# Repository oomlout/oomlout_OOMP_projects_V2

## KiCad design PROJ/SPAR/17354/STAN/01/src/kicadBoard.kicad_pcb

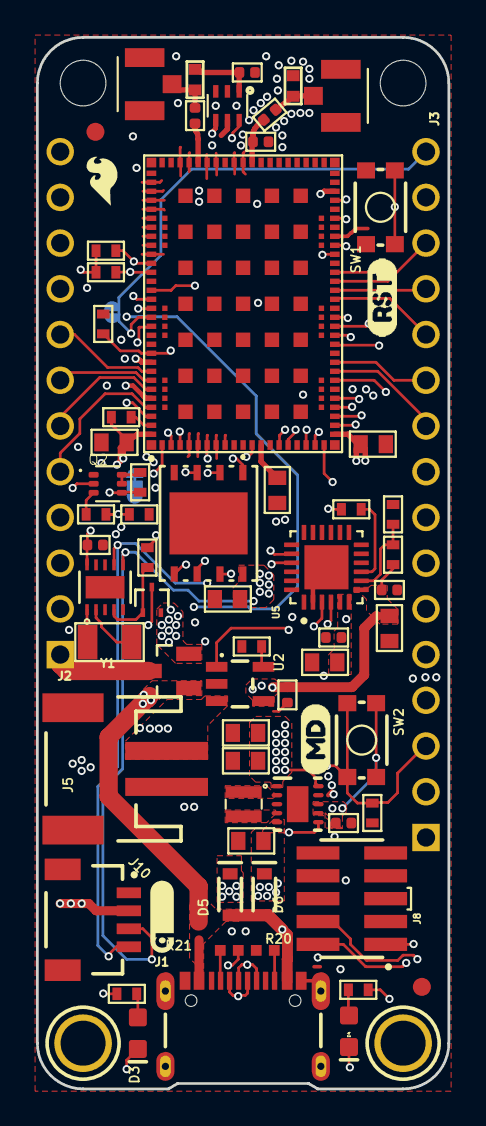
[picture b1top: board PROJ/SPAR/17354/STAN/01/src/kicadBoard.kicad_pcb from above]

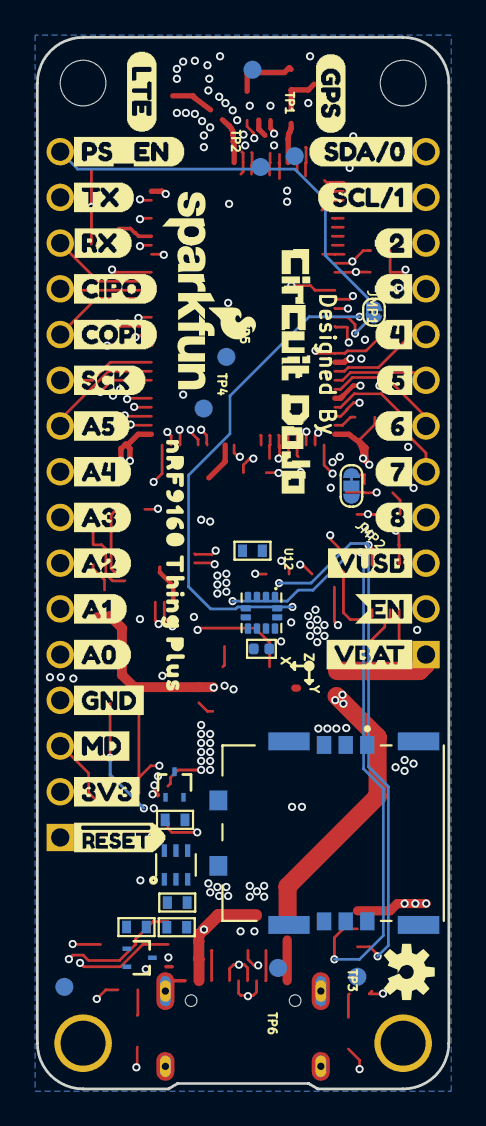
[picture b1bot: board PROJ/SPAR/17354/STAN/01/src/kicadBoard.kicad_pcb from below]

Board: 4 copper layers, 22.9 x 58.4 mm, 130 parts (55 on the bottom side), 79 nets.

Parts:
@HOLE0, @HOLE1: (no value)
C1, C2: 15p; CAPC1005X55N
C3, C8, C9, C10, C13, C15: 4.7u; C0603
C4, C5, C7: 10u; C0603
C6, C14, C16, C17, C20: 0.1u; CAPC1005X55N
C11: 1u; CAPC1005X55N
C12, C19: 56p; CAPC1005X55N
D3: BLUE; LED-0603
D4: Yellow; LED-0603
D5, D6: 1A/23V/620mV; SOD-323
J1: USB Female C; USB-C-16P_4LAYER-PADS
J2: CON-HEADER-1X12-MALE-PIN
J3: CON-HEADER-1X16-MALE-PIN
J4, J7: CON-1909763-1; TE_1909763-1
J5: JST-2-SMD
J6: CON-SIM-104224-0820; MOLEX_104224-0820
J8: CON-FTSH-105-XX-X-DV; SAMTEC_FTSH-105-XX-X-DV
J10: QWIIC_RIGHT_ANGLE; JST04_1MM_RA
JMP1: JUMPER-NC; JUMPER-ROUND-NC
JMP2: JUMPER-3/1; JUMPER-ROUND-3-NO-R
L1: 39n; IND0402_22N_TAI
L2: 1.5u; IND-2P0X2P0X1P2
L4: 68n; IND0402_22N_TAI
LOGO5: OSHW-LOGOS; OSHW-LOGO-S
PCB1: PCB-NRF91-FEATHER; PLACEHOLDER
Q1: MOSFET-P-SC89; DIO_RB558WMF-L
Q2: MOSFET-DUAL-COMP-SOT563; SOT50P160X60-6N
Q3: MOSFET-P-20V-4.7A-SOT23; SOT23
Q4, Q5: MOSFET-N-SC89; DIO_RB558WMF-L
R1, R3, R5, R6, R7, R8, R10, R13, R23: 100k; R0402-M
R2, R9, R19: 1M; R0402-M
R4: 1k; R0402-M
R11, R14: 330; R0402-M
R12: 2k; R0402-M
R15: 22k; R0402-M
R16: 33k; R0402-M
R17, R18: 10k; R0402-M
R20, R21: 5.1k; 0402-TIGHT
SW1, SW2: TACTILE_SWITCH_SMD_4.6X2.8MM
TP1, TP2, TP3, TP4, TP5, TP6: TP-1SIDE-1P0; TP-1P0
U1: MOD-NRF9160-SICA-R; NORDIC_NRF9160-SICA-R
U2: MCP73831; SOT23-5
U3: IC-TPS63031DSKR; DSK0010A
U4: POWER-SWITCH-MIC94092YC6; SOT363
U5: IC-CP2102N-A02-GQFN24R; QFN50P400X400X80-25N
U6: FLASH-WSON; WIN_ZP-8-L
U8: IC-PCF85063ATL/1; DFN10_2P7X2P7-L
U9: IC-BAV70S; SOT363
U12: IC-LIS2DH12TR; PQFN50P200X200100-12N
U$1: SFE_LOGO_NAME_FLAME_.1
U$2: LOGO-CIRCUITDOJO
U$3, U$4, U$24, U$35: FIDUCIAL-1MM
U$5: A3L-LOC
U$6: QWIIC_4MM
U$7: RST0
U$8: PS_EN0
U$9, U$14: MD0
U$10: 20
U$11: 30
U$12: SCL#11
U$13: SDA#00
U$15: SFE_LOGO_FLAME_.1
U$16: TX0
U$17: RX0
U$18: SCK0
U$19: CIPO0
U$20: COPI0
U$21: GPS0
U$22: LTE0
U$23: NRF9160_THING_PLUS0
U$31, U$32: MOUNTING-HOLE-2.5MM-PLATED
U$69: GND12
U$71: 3V314
U$72: #RESET15
U$73: VUSB25
U$74: EN26
U$75: VBAT27
U$83: A56
U$84: A47
U$85: A38
U$86: A29
U$87: A110
U$88: A011
U$89: 412
U$90: 513
U$91: 614
U$92: 715
U$93: 816
Y1: XTAL-ABS07AIG-32.768KHZ-7-T; XTAL320X150X90

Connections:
+3V3: C3.1, C4.1, C5.1, C8.1, C10.1, C20.1, J3.2, J8.1, J10.2, R9.2, R11.2, R14.2, R17.2, R18.2, R23.2, U1.12, U1.22, U1.102, U3.1, U3.10, U4.4, U6.8, U12.9, U12.10
ANT: C1.2, C2.1, U1.61
ANT_FILT: C1.1, J4.1, L1.2
CHRG: D4.C, U2.1
COEX0/LNA_EN: R1.2, U1.93, U4.6
CP212_VBUS: R15.1, R16.2, U5.8
CP2102N-VDD: C15.1, C16.1, R4.2, U5.5, U5.6
CP2102N-~RST: R4.1, U5.9
DIFF_N: J1.A7, J1.B7, U5.4
DIFF_P: J1.A6, J1.B6, U5.3
FLASH_CS: U1.4, U6.1
FLASH_HOLD: U1.18, U6.7
FLASH_SCK: U1.19, U6.6
FLASH_SI: U1.16, U6.5
FLASH_SO: U1.86, U6.2
FLASH_WP: U1.15, U6.3
GND: C2.2, C3.2, C4.2, C5.2, C6.2, C7.2, C8.2, C9.2, C10.2, C11.2, C13.2, C14.2, C15.2, C16.2, C17.2, C19.2, C20.2, J1.GND, J1.GND2, J1.SHLD1, J1.SHLD2, J1.SHLD3, J1.SHLD4, J3.4, J4.2, J4.3, J5.1, J6.G1, J6.G2, J6.G3, J6.G4, J6.S4, J7.2, J7.3, J8.3, J8.5, J8.9, J10.1, L1.1, Q2.1, Q4.2, Q5.2, R1.1, R2.1, R7.1, R8.1, R12.1, R13.1, R16.1, R19.1, R20.1, R21.1, SW1.3, SW1.4, U1.1, U1.5, U1.6, U1.7, U1.8, U1.9, U1.11, U1.14, U1.17, U1.21, U1.27, U1.31, U1.36, U1.41, U1.44, U1.47, U1.50, U1.52, U1.56, U1.60, U1.62, U1.63, U1.65, U1.66, U1.68, U1.69, U1.72, U1.74, U1.75, U1.76, U1.77, U1.78, U1.79, U1.80, U1.81, U1.82, U1.85, U1.90, U1.94, U1.98, U1.103_1, U1.103_2, U1.103_3, U1.103_4, U1.103_5, U1.103_6, U1.103_7, U1.103_8, U1.103_9, U1.103_10, U1.103_11, U1.103_12, U1.103_13, U1.103_14, U1.103_15, U1.103_16, U1.103_17, U1.103_18, U1.103_19, U1.103_20, U1.103_21, U1.103_22, U1.103_23, U1.103_24, U1.103_25, U1.103_26, U1.103_27, U1.103_28, U1.103_29, U1.103_30, U1.103_31, U1.103_32, U1.103_33, U1.103_34, U1.103_35, U2.2, U3.3, U3.9, U3.11, U4.2, U4.5, U5.2, U5.25, U6.4, U8.3, U8.5, U8.11, U12.3, U12.5, U12.6, U12.7, U12.8
GPS: C12.1, U1.67
GPS_ANT: C12.2, J7.1, L4.2
LNA_SW_OUT: C19.1, L4.1, U4.1
MODE/WAKE: J3.3, Q4.1, R13.2, SW2.3, SW2.4, U9.4
unnamed: L2.P$1, U3.4
unnamed: L2.P$2, U3.2
unnamed: J1.A5, R21.2
unnamed: R9.1, U1.101
unnamed: C9.1, U1.13
unnamed: Q2.3, R3.2
unnamed: Q2.5, Q2.6, R10.1
unnamed: D3.A, R11.1
unnamed: J1.B5, R20.2
unnamed: U8.1, Y1.2
unnamed: R23.1, U12.2
unnamed: JMP1.P$1, U12.12
unnamed: D4.A, R14.1
unnamed: U8.2, Y1.1
NRF_PS_EN_JMP: JMP2.P$2, U9.1
P0.00/D4: J2.8, U1.95
P0.01/D5: J2.7, U1.96
P0.02/D6: J2.6, U1.97
P0.03/D7: D3.C, J2.5, U1.99
P0.04/D8: J2.4, U1.100
P0.05/USB_UART_RX: U1.2, U5.21
P0.06/USB_UART_TX: U1.3, U5.20
P0.12/MD: Q4.3, U1.20
P0.13/A0: J3.5, U1.23
P0.14/A1: J3.6, U1.24
P0.15/A2: J3.7, U1.25
P0.16/A3: J3.8, U1.26
P0.17/A4: J3.9, U1.28
P0.18/A5: J3.10, U1.29
P0.19/SCK: J3.11, U1.30
P0.20/VBAT_MEAS: R3.1, R8.2, U1.35
P0.21/COPI: J3.12, U1.37
P0.22/CIPO: J3.13, U1.38
P0.23/RX: J3.14, U1.39
P0.24/TX: J3.15, U1.40
P0.25/VBAT_MEAS_EN: Q2.2, U1.42
P0.26/SDA: J2.12, J10.3, R17.1, U1.83, U8.6, U12.4
P0.27/SCL: J2.11, J10.4, R18.1, U1.84, U8.7, U12.1
P0.29/D2: J2.10, JMP1.P$2, U1.87
P0.30/D3: J2.9, U1.88
P0.31/NRF_PS_EN: J3.16, JMP2.P$3, U1.89
PROG: R12.2, U2.5
PS_EN: Q5.3, R5.1, U3.6
PS_EN_CC: R2.2, R5.2, U9.3, U9.6
RTC_INT: Q1.1, R6.1, U8.4
RTC_PS_EN: Q1.3, U9.5
SIM_CLK: J6.S3, TP3.TP, U1.46
SIM_IO: J6.S6, TP6.TP, U1.48
SIM_RST: J6.S2, TP4.TP, U1.43
SIM_VCC: J6.S1, TP5.TP, U1.49
SWCLK: J8.4, TP2.TP, U1.33
SWDIO: J8.2, TP1.TP, U1.34
VBAT: J2.1, J5.2, Q2.4, Q3.3, R10.2, U2.3
VBUS: C11.1, C13.1, C14.1, D5.A, D6.A, J1.VBUS1, J1.VBUS2, Q3.1, R7.2, R15.2, U2.4, U5.7, U9.2
VCC_5V0: D5.C, J2.3
VSYS: C6.1, C7.1, C17.1, D6.C, JMP2.P$1, Q1.2, Q3.2, R6.2, SW2.1, SW2.2, U3.5, U3.7, U3.8, U8.10
~EN: J2.2, Q5.1, R19.2
~RESET: J3.1, SW1.1, SW1.2, U1.32

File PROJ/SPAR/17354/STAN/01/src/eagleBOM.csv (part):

"Part";"Value";"Device";"Package";"Description";"ALIAS";"AVAILABILITY";"CURRENT";"DESC";"DESCRIPTION";"DIGIKEYPN";"MF";"MPN";"PACKAGE";"POWER";"PRICE";"PROD_ID";"PURCHASE-URL";"SF_ID";"TEMPHIGH";"TEMPLOW";"TOLERANCE";"VALUE";"VOLTHIGH";"VOLTLOW";
"C1";"15p";"CAP-15P-50V-0402";"CAPC1005X55N";"CAPACITOR";"";"";"";"CAP CER 15PF 50V C0G/NPO 0402";"";"311-1017-1-ND";"Yageo";"CC0402JRNPO9BN150";"";"";"";"CAP-13063";"";"";"";"";"";"15p";"50V";"";
"C2";"15p";"CAP-15P-50V-0402";"CAPC1005X55N";"CAPACITOR";"";"";"";"CAP CER 15PF 50V C0G/NPO 0402";"";"311-1017-1-ND";"Yageo";"CC0402JRNPO9BN150";"";"";"";"CAP-13063";"";"";"";"";"";"15p";"50V";"";
"C3";"4.7u";"CAP-4.7U-6.3V-2-0603";"C0603";"CAPACITOR";"";"";"";"CAP CER 4.7UF 6.3V X7R 0603";"";"587-4906-1-ND";"";"JMK107BB7475MA-T";"";"";"";"CAP-08280";"";"";"125";"-55";"";"4.7u";"6.3V";"";
"C4";"10u";"CAP-10U-6.3V-0603";"C0603";"CAPACITOR";"";"";"";"CAP CER 10UF 6.3V X5R 0603";"";"587-5869-1-ND";"";"JMK107ABJ106MA-T";"";"";"";"CAP-11015";"";"";"";"";"";"10u";"6.3";"";
"C5";"10u";"CAP-10U-6.3V-0603";"C0603";"CAPACITOR";"";"";"";"CAP CER 10UF 6.3V X5R 0603";"";"587-5869-1-ND";"";"JMK107ABJ106MA-T";"";"";"";"CAP-11015";"";"";"";"";"";"10u";"6.3";"";
"C6";"0.1u";"CAP-0.1U-50V-0402";"CAPC1005X55N";"CAPACITOR";"";"";"";"CAP CER 0.1UF 50V X5R 0402";"";"587-3499-1-ND";"Taiyo Yuden";"UMK105BJ104KV-F";"";"";"";"CAP-15083";"";"";"";"";"";"0.1u";"50V";"";
"C7";"10u";"CAP-10U-6.3V-0603";"C0603";"CAPACITOR";"";"";"";"CAP CER 10UF 6.3V X5R 0603";"";"587-5869-1-ND";"";"JMK107ABJ106MA-T";"";"";"";"CAP-11015";"";"";"";"";"";"10u";"6.3";"";
"C8";"4.7u";"CAP-4.7U-6.3V-2-0603";"C0603";"CAPACITOR";"";"";"";"CAP CER 4.7UF 6.3V X7R 0603";"";"587-4906-1-ND";"";"JMK107BB7475MA-T";"";"";"";"CAP-08280";"";"";"125";"-55";"";"4.7u";"6.3V";"";
"C9";"4.7u";"CAP-4.7U-6.3V-2-0603";"C0603";"CAPACITOR";"";"";"";"CAP CER 4.7UF 6.3V X7R 0603";"";"587-4906-1-ND";"";"JMK107BB7475MA-T";"";"";"";"CAP-08280";"";"";"125";"-55";"";"4.7u";"6.3V";"";
"C10";"4.7u";"CAP-4.7U-6.3V-2-0603";"C0603";"CAPACITOR";"";"";"";"CAP CER 4.7UF 6.3V X7R 0603";"";"587-4906-1-ND";"";"JMK107BB7475MA-T";"";"";"";"CAP-08280";"";"";"125";"-55";"";"4.7u";"6.3V";"";
"C11";"1u";"CAP-1U-25V-1-0402";"CAPC1005X55N";"CAPACITOR";"";"";"";"CAP CER 1UF 25V X5R 0402";"";"445-9081-1-ND";"TDK";"C1005X5R1E105M050BC";"";"";"";"CAP-12417";"";"";"";"";"";"1u";"25V";"";
"C12";"56p";"CAP-56PF-50V-0402";"CAPC1005X55N";"CAPACITOR";"";"";"";"CAP CER 56PF 50V C0G/NP0 0402";"";"399-1020-1-ND‎";"Kemet";"C0402C560J5GACTU‎";"";"";"";"CAP-15409";"";"";"";"";"";"56p";"50V";"";
"C13";"4.7u";"CAP-4.7U-6.3V-2-0603";"C0603";"CAPACITOR";"";"";"";"CAP CER 4.7UF 6.3V X7R 0603";"";"587-4906-1-ND";"";"JMK107BB7475MA-T";"";"";"";"CAP-08280";"";"";"125";"-55";"";"4.7u";"6.3V";"";
"C14";"0.1u";"CAP-0.1U-50V-0402";"CAPC1005X55N";"CAPACITOR";"";"";"";"CAP CER 0.1UF 50V X5R 0402";"";"587-3499-1-ND";"Taiyo Yuden";"UMK105BJ104KV-F";"";"";"";"CAP-15083";"";"";"";"";"";"0.1u";"50V";"";
"C15";"4.7u";"CAP-4.7U-6.3V-2-0603";"C0603";"CAPACITOR";"";"";"";"CAP CER 4.7UF 6.3V X7R 0603";"";"587-4906-1-ND";"";"JMK107BB7475MA-T";"";"";"";"CAP-08280";"";"";"125";"-55";"";"4.7u";"6.3V";"";
"C16";"0.1u";"CAP-0.1U-50V-0402";"CAPC1005X55N";"CAPACITOR";"";"";"";"CAP CER 0.1UF 50V X5R 0402";"";"587-3499-1-ND";"Taiyo Yuden";"UMK105BJ104KV-F";"";"";"";"CAP-15083";"";"";"";"";"";"0.1u";"50V";"";
"C17";"0.1u";"CAP-0.1U-50V-0402";"CAPC1005X55N";"CAPACITOR";"";"";"";"CAP CER 0.1UF 50V X5R 0402";"";"587-3499-1-ND";"Taiyo Yuden";"UMK105BJ104KV-F";"";"";"";"CAP-15083";"";"";"";"";"";"0.1u";"50V";"";
"C19";"56p";"CAP-56PF-50V-0402";"CAPC1005X55N";"CAPACITOR";"";"";"";"CAP CER 56PF 50V C0G/NP0 0402";"";"399-1020-1-ND‎";"Kemet";"C0402C560J5GACTU‎";"";"";"";"CAP-15409";"";"";"";"";"";"56p";"50V";"";
"C20";"0.1u";"CAP-0.1U-50V-0402";"CAPC1005X55N";"CAPACITOR";"";"";"";"CAP CER 0.1UF 50V X5R 0402";"";"587-3499-1-ND";"Taiyo Yuden";"UMK105BJ104KV-F";"";"";"";"CAP-15083";"";"";"";"";"";"0.1u";"50V";"";
"D3";"BLUE";"LED-BLUE0603";"LED-0603";"Blue SMD LED";"";"";"";"";"";"";"";"";"";"";"";"DIO-08575";"";"";"";"";"";"BLUE";"";"";
"D4";"Yellow";"LED-YELLOW0603";"LED-0603";"Yellow SMD LED";"";"";"";"";"";"";"";"";"";"";"";"DIO-09003";"";"";"";"";"";"Yellow";"";"";
"D5";"1A/23V/620mV";"DIODE-SCHOTTKY-BAT20J";"SOD-323";"Schottky diode";"";"";"";"";"";"";"";"";"";"";"";"DIO-11623";"";"";"";"";"";"1A/23V/620mV";"";"";
"D6";"1A/23V/620mV";"DIODE-SCHOTTKY-BAT20J";"SOD-323";"Schottky diode";"";"";"";"";"";"";"";"";"";"";"";"DIO-11623";"";"";"";"";"";"1A/23V/620mV";"";"";
"J1";"USB Female C";"USB_C_4-LAYER_PADS";"USB-C-16P_4LAYER-PADS";"USB Type C 16Pin Connector";"";"";"";"";"";"";"";"";"";"";"";"CONN-14122";"";"";"";"";"";"";"";"";
"J2";"CON-HEADER-1X12-MALE-PIN";"CON-HEADER-1X12-MALE-PIN";"CON-HEADER-1X12-MALE-PIN";"";"POGO-1.9MM-S19-501";"";"";"";"";"";"";"";"";"";"";"";"";"";"";"";"";"";"";"";
"J3";"CON-HEADER-1X16-MALE-PIN";"CON-HEADER-1X16-MALE-PIN";"CON-HEADER-1X16-MALE-PIN";"";"";"";"";"";"";"";"";"";"";"";"";"";"";"";"";"";"";"";"";"";
"J4";"CON-1909763-1";"CON-1909763-1";"TE_1909763-1";"VAO ITEM, MINI RF HEADER";"";"";"";"CONN UMCC JACK STR 50OHM SMD";"";"A118077CT-ND";"TE Connectivity";"1909763-1";"";"";"";"CONN-15410 ";"";"";"";"";"";"";"";"";
"J5";"";"JST_2MM_MALE";"JST-2-SMD";"JST 2MM MALE RA CONNECTOR";"";"";"";"";"";"";"";"";"";"";"";"CONN-11443";"";"PRT-08612";"";"";"";"";"";"";
"J6";"CON-SIM-104224-0820";"CON-SIM-104224-0820";"MOLEX_104224-0820";"Conn SIM SKT 6 POS 2.54mm Solder RA SMD";"";"";"";"NANOSIM SOCKET 1.11H P/PULL TYPE";" 6 Position Card Connector NANO SIM Surface Mount, Right Angle Gold ";"";"Molex";"104224-0820";"None";"";"None";"CONN-15682";"";"";"";"";"";"";"";"";
"J7";"CON-1909763-1";"CON-1909763-1";"TE_1909763-1";"VAO ITEM, MINI RF HEADER";"";"";"";"CONN UMCC JACK STR 50OHM SMD";"";"A118077CT-ND";"TE Connectivity";"1909763-1";"";"";"";"CONN-15410 ";"";"";"";"";"";"";"";"";
"J8";"CON-FTSH-105-XX-X-DV";"CON-FTSH-105-XX-X-DV";"SAMTEC_FTSH-105-XX-X-DV";"Connector Header Surface Mount 10 position 0.050" (1.27mm)  Check prices";"";"";"";"";" Connector Header Surface Mount 10 position 0.050 (1.27mm) ";"SAM8796-ND";"Samtec";"FTSH-105-01-F-DV-K";"";"";"None";"CONN-15353";"https://pricing.snapeda.com/search/part/FTSH-105-01-F-DV-K/?ref=eda";"";"";"";"";"";"";"";
"J10";"QWIIC_RIGHT_ANGLE";"QWIIC_CONNECTORJS-1MM";"JST04_1MM_RA";"SparkFun I2C Standard Qwiic Connector";"";"";"";"";"";"";"";"";"";"";"";"CONN-13694";"";"";"";"";"";"QWIIC_RIGHT_ANGLE";"";"";
"JMP1";"JUMPER-NC";"JUMPER-NC";"JUMPER-ROUND-NC";"";"";"";"";"";"";"";"";"";"";"";"";"";"";"";"";"";"";"";"";"";
"JMP2";"JUMPER-3/1";"JUMPER-3/1";"JUMPER-ROUND-3-NO-R";"";"";"";"";"";"";"";"";"";"";"";"";"";"";"";"";"";"";"";"";"";
"L1";"39n";"IND-39NH-250MA-0402";"IND0402_22N_TAI";"INDUCTOR";"";"";"250mA";"FIXED IND 39NH 250MA 1.06 OHM";"";"490-1092-1-ND";"";"LQG15HN39NJ02D";"";"";"";"NDUC-15408";"";"";"";"";"";"39n";"";"";
"L2";"1.5u";"IND-1.5U-1.4A-2X2";"IND-2P0X2P0X1P2";"FIXED IND 1.5UH 1.4A 120 MOHM";"";"";"1.4A";"FIXED IND 1.5UH 1.4A 120 MOHM";"";"587-4702-1-ND";"";"NRV2012T1R5NGF";"";"";"";"NDUC-15405";"";"";"";"";"";"1.5u";"";"";
"L4";"68n";"IND-68NH-200MA-0402";"IND0402_22N_TAI";"INDUCTOR";"";"";"200mA";"FIXED IND 68NH 200MA 1.25 OHM";"";"‎490-15092-1-ND‎";"";"LQG15HN68NH02D‎";"";"";"";"NDUC-15356";"";"";"";"";"";"68n";"";"";
"PCB1";"PCB-NRF91-FEATHER";"PCB-NRF91-FEATHER";"PLACEHOLDER";"";"";"";"";"";"";"";"";"BRD-0015";"";"";"";"";"";"";"";"";"";"";"";"";
"Q1";"MOSFET-P-SC89";"MOSFET-P-SC89";"DIO_RB558WMF-L";"MOSFET P-CH";"";"";"";"MOSFET P-CH 20V 0.1A EMT3";"";"RE1C001ZPTLCT-ND";"";"RE1C001ZPTL";"";"";"";"TRANS-15421";"";"";"";"";"";"";"";"";
"Q2";"MOSFET-DUAL-COMP-SOT563";"MOSFET-DUAL-COMP-SOT563";"SOT50P160X60-6N";"";"";"";"";"MOSFET N/P-CH 60V/50V SOT666";"";"1727-1277-1-ND";"";"NX1029X,115";"";"";"";"IC-15419";"";"";"";"";"";"";"";"";
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
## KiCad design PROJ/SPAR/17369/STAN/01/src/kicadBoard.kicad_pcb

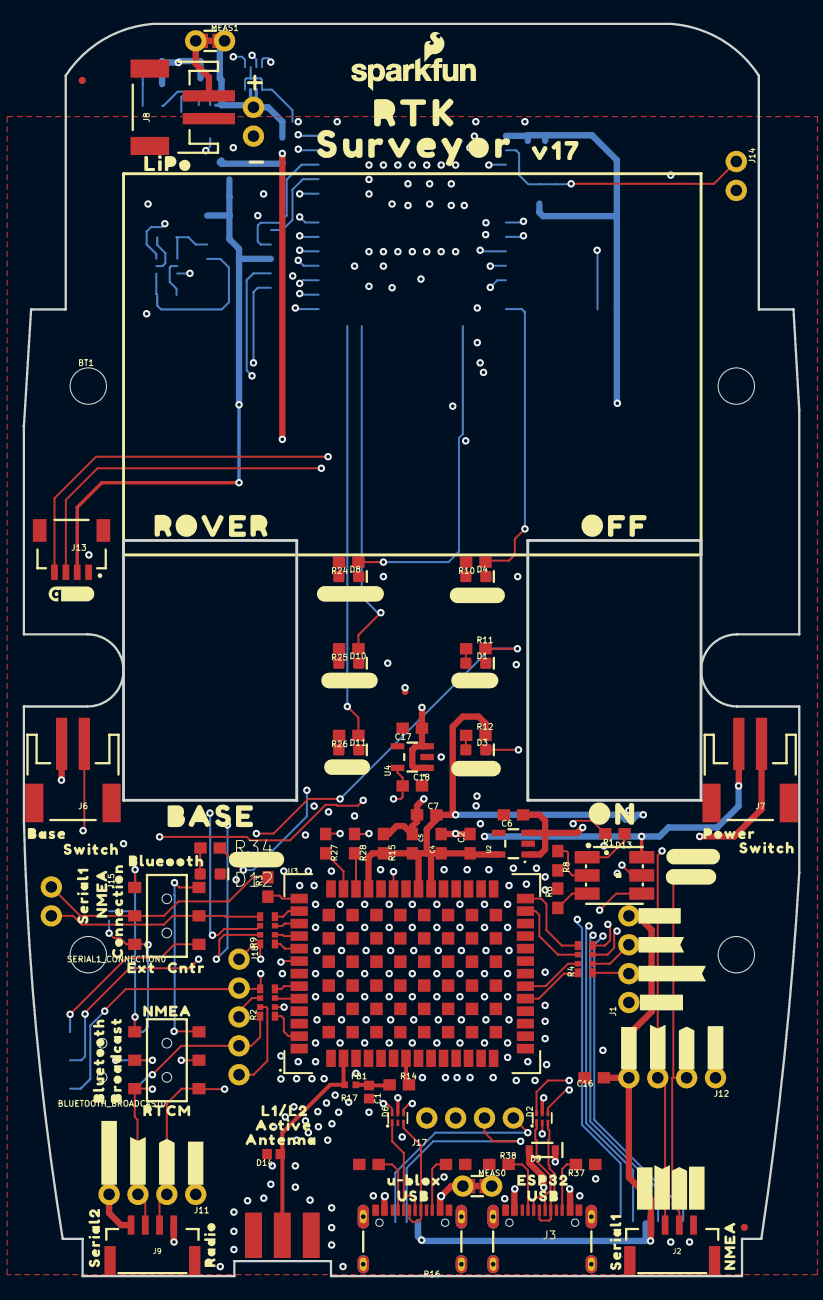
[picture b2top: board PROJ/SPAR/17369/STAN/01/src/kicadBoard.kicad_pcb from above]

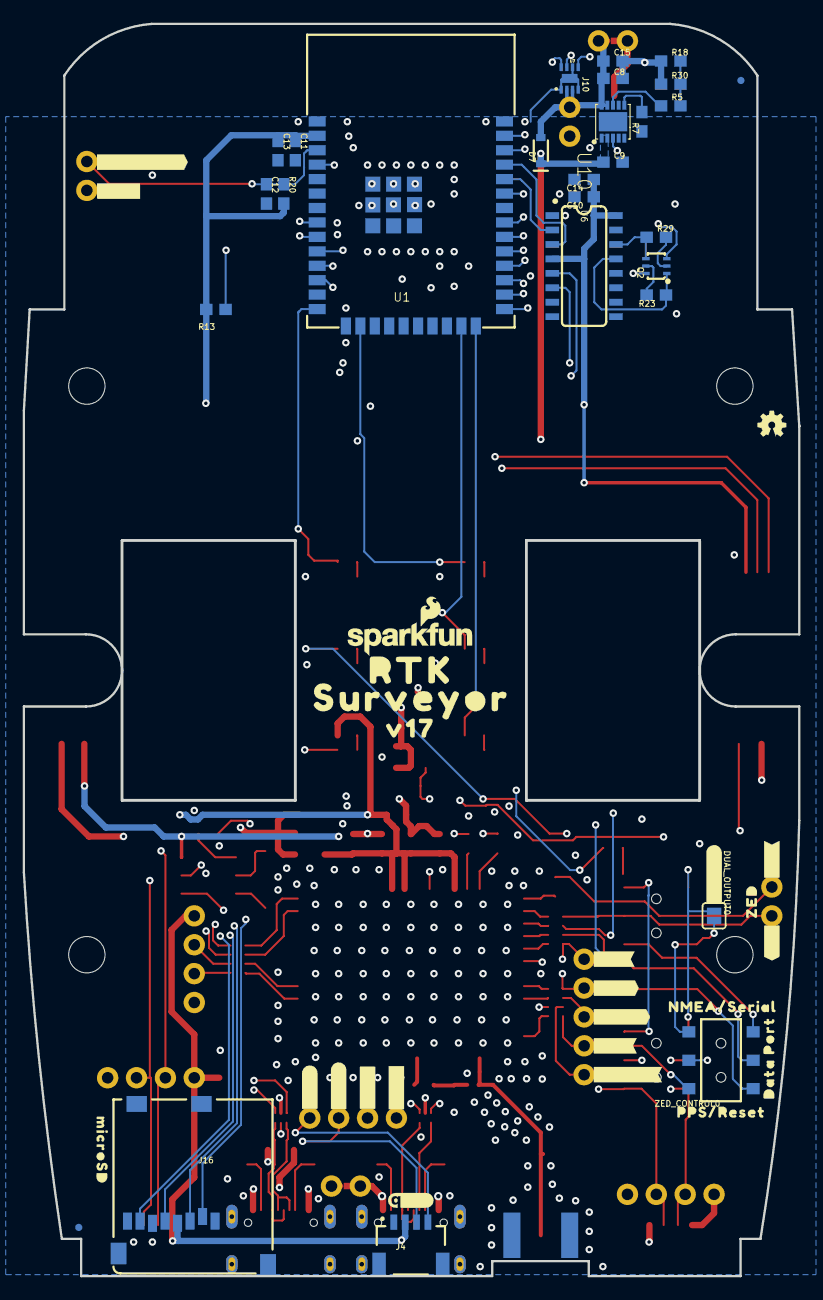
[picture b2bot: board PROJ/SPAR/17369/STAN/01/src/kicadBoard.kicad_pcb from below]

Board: 4 copper layers, 68.2 x 110.1 mm, 199 parts (55 on the bottom side), 95 nets.

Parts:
BLUETOOTH_BROADCAST0: SWITCH_DPDT_SMD_AYZ0202
BT1: LIPO-OUTLINE1000; LIPO-1000
C1: 47pF; 0402
C2, C4, C6, C17, C18: 1.0uF; 0603
C5, C7, C11, C12, C13, C15, C16: 0.1uF; 0603
C8, C9: 4.7uF; 0603
C10, C14: 10uF; 0603
D1: Yellow; LED-0603
D2, D6: PRTR5V0U2F; SOT886
D3: WHITE; LED-0603
D4: BLUE; LED-0603
D7, D9: 3A/10V/280mV; SOD-323
D8, D10, D11: GREEN; LED-0603
D12: RED; LED-0603
D13: LED-TRICOLOR-5050
D14: PESD0402; 0402
DUAL_OUTPUT0: SMT-JUMPER_2_NO_SILK
E1: SMA; SMA-EDGE
FB1: 2.66Ω; 0402-TIGHT
FRAME1: FRAME-LETTERNO_PACKAGE; DUMMY
FRAME2: FRAME-LEDGER; CREATIVE_COMMONS
J1, J11, J12: 1X04_NO_SILK
J2, J9: JST-4-SMD-1.25MM-LOCKING
J3, J5: USB Female Type C Connector; USB-C-16P_4LAYER-PADS
J4: Qwiic Right Angle; JST04_1MM_RA
J6: Start Base; JST-2-SMD
J7: Power Switch; JST-2-SMD
J8: JST-2-SMD
J10, J14, J15: 1X02_NO_SILK
J13: Internal; JST04_1MM_RA
J16: microSD; MICRO-SD-SOCKET
J17: Qwiic Right Angle; 1X04_NO_SILK
J18: 1X05_NO_SILK
JP21, JP61, JP71, JP81: FIDUCIALUFIDUCIAL; FIDUCIAL-MICRO
LOGO1: OSHW-LOGOMINI; OSHW-LOGO-MINI
LOGO2, LOGO3: SFE_LOGO_NAME_FLAME.1_INCH; SFE_LOGO_NAME_FLAME_.1
MEAS0, MEAS1: COMBO-JUMPER_2_NC_TRACE
Q2: MBT3904DW1T1; SC70-6
R1: 4.7k; 0603
R2, R4, R9: 33; 1206_RA
R3: 33; 0603
R5: 0; 0603
R6, R7, R8: 1k; 0603
R10, R12, R34: 330; 0603
R11, R24, R25, R26: 20; 0603
R13, R15: 100k; 0603
R14: 10; 0603
R16, R17, R37, R38: 5.1k; 0603
R18, R20, R23, R29: 10k; 0603
R27, R28: 27; 0603
R30: 150k; 0603
SERIAL1_CONNECTION0: SWITCH_DPDT_SMD_AYZ0202
U1: ESP-WROOM-3232D-NARROW; ESP-WROOM-32D-NARROW
U2, U4: 3.3V; SOT23-5
U3: U-BLOX_ZED-F9P; ZED-F9P
U6: CH340C; SO016
U7: MAX17048; DFN-8
U10: MCP73833; DFN-10
U$1, U$38, U$48, U$82: #GND#0
U$2: SPECIAL_INSTRUCTIONS-ORDERING; ORDERING_INSTRUCTIONS
U$3, U$34: ROCKER_SWITCH
U$4: #BASE#0
U$5, U$37, U$47: #3V3#0
U$6: ANTENNA0
U$7, U$74: RTK0
U$8: #CHG#0
U$9, U$71: _SURVEYOR3
U$10: #RTK#1
U$11: #PPS#0
U$12: #RTK#0
U$13, U$15, U$21, U$69, U$75, U$76, U$77, U$78: LIGHT_PIPE_3MM
U$14: #RX#2
U$16: ZED0
U$17: ##SAFE##5
U$18: ACTIVE0
U$19: L1#L21
U$20: #PAIR#0
U$22: BASE2
U$23: #3#5#5V#0
U$24: #PPS#1
U$25: #PWR#2
U$26: 1553DBK-ENCLOSURE
U$27: LIPO0
U$28: ##RST##4
U$29, U$63: SERIAL10
U$30, U$93: QWIIC_4MM
U$31: OFF1
U$32: #FENCE#3
U$33: #INT#0
U$35: U#BLOX0
U$36, U$66: USB1
U$39: #RX2#2
U$40: #TX2#1
U$41: BLUETOOTH2
U$42: ON0
U$43: SERIAL20
U$44: ROVER3
U$45, U$68: #RX1#2
U$46, U$65: #TX1#1
U$49, U$52: NMEA1
U$50: RADIO0
U$51: BROADCAST3
U$53: RTCM0
U$54: BASE0
U$55, U$57: SWITCH1
U$56: POWER0
U$58: BLUEOOTH3
U$59: CNTR1
U$60: #ESP_RST#0
U$61: EXT0
U$62: NMEA2
U$64: CONNECTION1
U$67: ESP320
U$70: #GND#2
U$72: #TX#1
U$73: #DUAL#0
U$79: #1CM#0
U$80: #10CM#1
U$81: #100CM#2
U$83: MICROSD0
U$84: #GND#1
U$85: #3V3#2
U$86: #SCL#1
U$87: #SDA#0
U$88: #D_SEL#0
U$89: DATA2
U$90: PORT3
U$91: PPS#RESET0
U$92: NMEA#SERIAL1
U$94, U$95: V170
ZED_CONTROL0: SWITCH_DPDT_SMD_AYZ0202

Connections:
3.3V: C2.1, C4.1, C5.2, C7.2, C10.1, C11.1, C13.1, C14.1, C16.1, J1.4, J2.1, J4.2, J12.4, J13.2, J16.VCC, J17.2, R12.2, R13.2, R15.2, R20.2, U1.2, U2.5, U3.33, U3.34, U3.38, U6.4, U6.16
5V: C6.1, J7.1, J9.1, J11.4, U2.1, U2.3
ANT_VCC: C1.1, FB1.2, R14.1
BACKUP: C18.1, U3.36, U4.5
CC1: J5.A5, R17.2
CC2: J5.B5, R16.2
CC3: J3.B5, R37.2
CC4: J3.A5, R38.2
CHG_LED: R1.2, U10.3
CHG_THERM1: R5.2, R18.2, R30.2
D+: D6.4, R27.1
D+1: D2.4, U6.5
D-: D6.6, R28.1
D-1: D2.6, U6.6
ESP32_EN: C12.1, J14.1, Q2.3, R20.1, U1.3
ESP32_RXI: U1.34, U6.2
ESP32_TXO: U1.35, U6.3
ESP32_~DTR: Q2.1, R23.1, U6.13
ESP32_~RTS: Q2.4, R29.1, U6.14
ESP_0/BOOT: Q2.6, U1.25
ESP_2/LED_1CM: R26.1, U1.24
ESP_4/LED_BASE_STAT: R34.1, U1.26
ESP_5/SWITCH_BASE_SELECT: J6.1, U1.29
ESP_12/LED_BLUETOOTH: R10.1, U1.14
ESP_13/LED_100CM: R24.1, U1.16
ESP_15/LED_10CM: R25.1, U1.23
ESP_16/BT_RXI: BLUETOOTH_BROADCAST0.2, U1.27
ESP_17/BT_TXO: BLUETOOTH_BROADCAST0.5, U1.28
ESP_18/SD_SCK: J16.SCLK, U1.30
ESP_19/SD_CIPO: J16.DO/DAT0, U1.31
ESP_21/SDA: J4.3, J13.3, J17.3, R9.P6, U1.33, U7.8
ESP_22/SCL: J4.4, J13.4, J17.4, R9.P7, U1.36, U7.7
ESP_23/SD_COPI: J16.DI/CMD, U1.37
ESP_25/SD_~CS: J16.CS/DAT3, R13.1, U1.10
ESP_26/ZED_TX_READY: J18.1, R9.P8, U1.11
ESP_26/ZED_TX_READY_LV: R9.P1, U3.46
ESP_27/ZED_~RESET: J18.2, R2.P5, U1.12, ZED_CONTROL0.4
ESP_27/ZED_~RESET_LV: R2.P4, U3.49
ESP_32/PWR_LVL_RED: D13.5, U1.8
ESP_33/PWR_LVL_GRN: D13.4, U1.9
ESP_36/BATT_ALRT: U1.4, U7.5
ESP_D1+: D2.3, J3.A6, J3.B6
ESP_D1-: D2.1, J3.A7, J3.B7
EXTERNAL_SERIAL1_RXI: SERIAL1_CONNECTION0.4, ZED_CONTROL0.6
EXTERNAL_SERIAL1_RXI/ZED_~RESET: J2.3, J12.2, ZED_CONTROL0.5
EXTERNAL_SERIAL1_TXO: DUAL_OUTPUT0.2, SERIAL1_CONNECTION0.1, ZED_CONTROL0.3
EXTERNAL_SERIAL1_TXO/PPS: J2.2, J12.3, ZED_CONTROL0.2
FENCE_LV: R4.P8, U3.19
GND: C1.2, C2.2, C4.2, C5.1, C6.2, C7.1, C8.2, C9.2, C10.2, C11.2, C12.2, C13.2, C14.2, C15.2, C16.2, C17.2, C18.2, D1.C, D2.2, D4.C, D6.2, D8.C, D10.C, D11.C, D12.C, D14.2, E1.GND@0, E1.GND@1, E1.GND@2, E1.GND@3, J1.1, J2.4, J3.GND, J3.GND2, J3.SHLD1, J3.SHLD2, J3.SHLD3, J3.SHLD4, J4.1, J5.GND, J5.GND2, J5.SHLD1, J5.SHLD2, J5.SHLD3, J5.SHLD4, J6.2, J8.1, J9.4, J10.2, J11.1, J12.1, J13.1, J14.2, J16.CD1, J16.GND, J16.GND1, J16.GND3, J17.1, R6.2, R7.1, R8.2, R15.1, R16.1, R17.1, R18.1, R30.1, R37.1, R38.1, U1.1, U1.15, U1.38, U1.GND1, U1.GNDT1, U1.GNDT2, U1.GNDT3, U1.GNDT4, U1.GNDT5, U1.GNDT6, U1.GNDT7, U1.GNDT8, U2.2, U3.1, U3.3, U3.12, U3.14, U3.32, U3.37, U3.41, U3.48, U3.55, U3.56, U3.57, U3.58, U3.59, U3.60, U3.61, U3.62, U3.63, U3.64, U3.65, U3.66, U3.67, U3.68, U3.69, U3.70, U3.71, U3.72, U3.73, U3.74, U3.75, U3.76, U3.77, U3.78, U3.79, U3.80, U3.81, U3.82, U3.83, U3.84, U3.85, U3.86, U3.87, U3.88, U3.89, U3.90, U3.91, U3.92, U3.93, U3.94, U3.95, U3.96, U3.97, U3.98, U3.99, U3.100, U3.101, U3.102, U4.2, U6.1, U7.1, U7.4, U7.6, U7.9, U10.5, U10.11
GPS_ANT1: D14.1, E1.SIG, FB1.1, U3.2
LIPO_RAW: J8.2, MEAS1.1, MEAS1.3
unnamed: D3.A, R12.1
unnamed: D1.A, R11.1
unnamed: D4.A, R10.2
unnamed: J5.VBUS1, J5.VBUS2, MEAS0.1, MEAS0.3
unnamed: R5.1, U10.8
unnamed: D13.1, R1.1
unnamed: D13.3, R6.1
unnamed: D13.2, R8.1
unnamed: R27.2, U3.40
unnamed: R28.2, U3.39
unnamed: R14.2, U3.7
unnamed: Q2.5, R23.2
unnamed: Q2.2, R29.2
unnamed: D8.A, R24.2
unnamed: D10.A, R25.2
unnamed: D11.A, R26.2
unnamed: D12.A, R34.2
unnamed: D9.A, J3.VBUS1, J3.VBUS2
NMEA-RX: BLUETOOTH_BROADCAST0.6, SERIAL1_CONNECTION0.6
NMEA-TX: BLUETOOTH_BROADCAST0.3, DUAL_OUTPUT0.1, SERIAL1_CONNECTION0.3
PPS: R2.P1, U3.53
PROG1: R7.2, U10.6
RTK_LV: R4.P7, U3.20
RX2_LV: R4.P6, U3.26
RXLV: R9.P4, U3.43
SCL_LV: R9.P2, U3.45
SDA_LV: R9.P3, U3.44
TX2_LV: R4.P5, U3.27
TXLV: R3.1, U3.42
UNP_D+: D6.3, J5.A6, J5.B6
UNP_D-: D6.1, J5.A7, J5.B7
VIN: C9.1, D2.5, D6.5, D7.C, D9.C, D13.6, J7.2, MEAS0.2, MEAS0.4, U10.1, U10.2
V_BATT: C8.1, C15.1, C17.1, D7.A, J10.1, MEAS1.2, MEAS1.4, U4.1, U4.3, U7.2, U7.3, U10.9, U10.10
ZED-RXI1: J15.2, R9.P5, SERIAL1_CONNECTION0.5
ZED-RXI2: BLUETOOTH_BROADCAST0.4, J9.3, J11.2, R4.P3
ZED-TXO1: J15.1, R3.2, SERIAL1_CONNECTION0.2
ZED-TXO2: BLUETOOTH_BROADCAST0.1, J9.2, J11.3, R4.P4
ZED_D_SEL: J18.5, R2.P7
ZED_D_SEL_LV: R2.P2, U3.47
ZED_FENCE_STAT: J1.2, R4.P1
ZED_PPS_STAT: J18.4, R2.P8, R11.2, ZED_CONTROL0.1
ZED_RTK_STAT: D3.C, J1.3, R4.P2
ZED_~SAFE: J18.3, R2.P6
ZED_~SAFE_LV: R2.P3, U3.50

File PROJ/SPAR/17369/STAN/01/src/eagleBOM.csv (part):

"Part";"Value";"Device";"Package";"Description";"DESIGNER";"DIGIKEY_PART";"MOUSE_PART";"PROD_ID";"REV";"SF_ID";"SF_SKU";"VALUE";"VERSION";
"BLUETOOTH_BROADCAST";"";"SWITCH-DPDT-SMD-AYZ0202";"SWITCH_DPDT_SMD_AYZ0202";"Double-Pole, Double-Throw (DPDT) Switch";"";"";"";"SWCH-08179";"";"";"COM-00597";"";"";
"BT1";"LIPO-OUTLINE1000";"LIPO-OUTLINE1000";"LIPO-1000";"LiPo Battery Outlines";"";"";"";"BATT-13243";"";"";"PRT-13813";"";"";
"C1";"47pF";"47PF-0402-25V-5%-X7R";"0402";"47pF ceramic capacitors";"";"";"";"CAP-15063";"";"";"";"47pF";"";
"C2";"1.0uF";"1.0UF-0603-16V-10%-X7R";"0603";"1µF ceramic capacitors";"";"";"";"CAP-13930";"";"";"";"1.0uF";"";
"C4";"1.0uF";"1.0UF-0603-16V-10%-X7R";"0603";"1µF ceramic capacitors";"";"";"";"CAP-13930";"";"";"";"1.0uF";"";
"C5";"0.1uF";"0.1UF-0603-25V-5%";"0603";"0.1µF ceramic capacitors";"";"";"";"CAP-08604";"";"";"";"0.1uF";"";
"C6";"1.0uF";"1.0UF-0603-16V-10%-X7R";"0603";"1µF ceramic capacitors";"";"";"";"CAP-13930";"";"";"";"1.0uF";"";
"C7";"0.1uF";"0.1UF-0603-25V-5%";"0603";"0.1µF ceramic capacitors";"";"";"";"CAP-08604";"";"";"";"0.1uF";"";
"C8";"4.7uF";"4.7UF-0603-35V-(20%)";"0603";"4.7µF ceramic capacitors";"";"";"";"CAP-14106";"";"";"";"4.7uF";"";
"C9";"4.7uF";"4.7UF-0603-35V-(20%)";"0603";"4.7µF ceramic capacitors";"";"";"";"CAP-14106";"";"";"";"4.7uF";"";
"C10";"10uF";"10UF-0603-6.3V-20%";"0603";"10.0µF ceramic capacitors";"";"";"";"CAP-11015";"";"";"";"10uF";"";
"C11";"0.1uF";"0.1UF-0603-25V-(+80/-20%)";"0603";"0.1µF ceramic capacitors";"";"";"";"CAP-00810";"";"";"";"0.1uF";"";
"C12";"0.1uF";"0.1UF-0603-25V-(+80/-20%)";"0603";"0.1µF ceramic capacitors";"";"";"";"CAP-00810";"";"";"";"0.1uF";"";
"C13";"0.1uF";"0.1UF-0603-25V-(+80/-20%)";"0603";"0.1µF ceramic capacitors";"";"";"";"CAP-00810";"";"";"";"0.1uF";"";
"C14";"10uF";"10UF-0603-6.3V-20%";"0603";"10.0µF ceramic capacitors";"";"";"";"CAP-11015";"";"";"";"10uF";"";
"C15";"0.1uF";"0.1UF-0603-25V-(+80/-20%)";"0603";"0.1µF ceramic capacitors";"";"";"";"CAP-00810";"";"";"";"0.1uF";"";
"C16";"0.1uF";"0.1UF-0603-25V-(+80/-20%)";"0603";"0.1µF ceramic capacitors";"";"";"";"CAP-00810";"";"";"";"0.1uF";"";
"C17";"1.0uF";"1.0UF-0603-16V-10%-X7R";"0603";"1µF ceramic capacitors";"";"";"";"CAP-13930";"";"";"";"1.0uF";"";
"C18";"1.0uF";"1.0UF-0603-16V-10%-X7R";"0603";"1µF ceramic capacitors";"";"";"";"CAP-13930";"";"";"";"1.0uF";"";
"D1";"Yellow";"LED-YELLOW0603";"LED-0603";"Yellow SMD LED";"";"";"";"DIO-09003";"";"";"";"Yellow";"";
"D2";"PRTR5V0U2F";"PRTR5V0U2F";"SOT886";"A small ESD protection device. Most commonly used on USB D+/D- signals to protect large, expensive, or especially sensitive USB enabled devices.";"";"";"";"DIO-14084";"";"";"";"";"";
"D3";"WHITE";"LED-WHITE0603";"LED-0603";"White SMD LED";"";"";"";"DIO-09004";"";"";"";"WHITE";"";
"D4";"BLUE";"LED-BLUE0603";"LED-0603";"Blue SMD LED";"";"";"";"DIO-08575";"";"";"";"BLUE";"";
"D6";"PRTR5V0U2F";"PRTR5V0U2F";"SOT886";"A small ESD protection device. Most commonly used on USB D+/D- signals to protect large, expensive, or especially sensitive USB enabled devices.";"";"";"";"DIO-14084";"";"";"";"";"";
"D7";"3A/10V/280mV";"DIODE-SCHOTTKY-BAT60A";"SOD-323";"Schottky diode";"";"";"";"DIO-14072";"";"";"";"3A/10V/280mV";"";
"D8";"GREEN";"LED-GREEN0603";"LED-0603";"Green SMD LED";"";"";"";"DIO-00821";"";"";"";"GREEN";"";
"D9";"3A/10V/280mV";"DIODE-SCHOTTKY-BAT60A";"SOD-323";"Schottky diode";"";"";"";"DIO-14072";"";"";"";"3A/10V/280mV";"";
"D10";"GREEN";"LED-GREEN0603";"LED-0603";"Green SMD LED";"";"";"";"DIO-00821";"";"";"";"GREEN";"";
"D11";"GREEN";"LED-GREEN0603";"LED-0603";"Green SMD LED";"";"";"";"DIO-00821";"";"";"";"GREEN";"";
"D12";"RED";"LED-RED0603";"LED-0603";"Red SMD LED";"";"";"";"DIO-00819";"";"";"";"RED";"";
"D13";"";"LED-RGBBRG";"LED-TRICOLOR-5050";"LED-RGB";"";"";"";"DIO-16048";"";"";"";"";"";
"D14";"PESD0402";"PESD0402";"0402";"ESD protection diode";"";"PESD0402-140CT-ND";"650-PESD0402-140";"DIO-15359";"";"";"";"";"";
"DUAL_OUTPUT";"";"JUMPER-SMT_2_NO_SILK";"SMT-JUMPER_2_NO_SILK";"Normally open jumper";"";"";"";"";"";"";"";"";"";
"E1";"SMA";"ANTENNA-SMA-GROUNDEDEDGE_SMA";"SMA-EDGE";"SMA Antenna Connector w/ Ground";"";"";"";"CONN-08289";"";"";"";"";"";
"FB1";"2.66Ω";"FERRITE_BEAD-0402-2.66Ω-1GHZ";"0402-TIGHT";"Ferrite Bead (blocks, cores, rings, chokes, etc.)";"";"";"";"NDUC-15072";"";"";"";"2.66Ω";"";
"FRAME1";"FRAME-LETTERNO_PACKAGE";"FRAME-LETTERNO_PACKAGE";"DUMMY";"Schematic Frame - Letter";"Nobody";"";"";"";"";"";"";"";"v01";
"FRAME2";"FRAME-LEDGER";"FRAME-LEDGER";"CREATIVE_COMMONS";"Schematic Frame - Ledger";"";"";"";"";"";"";"";"";"";
"J1";"";"CONN_041X04_NO_SILK_NO_POP";"1X04_NO_SILK";"Multi connection point. Often used as Generic Header-pin footprint for 0.1 inch spaced/style header connections";"";"";"";"";"";"";"";"";"";
"J2";"";"CONN_04JST-SMD-LOCKING";"JST-4-SMD-1.25MM-LOCKING";"Multi connection point. Often used as Generic Header-pin footprint for 0.1 inch spaced/style header connections";"";"";"";"CONN-15303";"";"";"";"";"";
"J3";"USB Female Type C Connector";"USB_C_4-LAYER_PADS";"USB-C-16P_4LAYER-PADS";"USB Type C 16Pin Connector";"";"";"";"CONN-14122";"";"";"";"";"";
"J4";"External";"I2C_STANDARDQWIIC";"JST04_1MM_RA";"SparkFun I2C Standard Pinout Header";"";"";"";"CONN-13694";"";"";"";"Qwiic Right Angle";"";
"J5";"USB Female Type C Connector";"USB_C_4-LAYER_PADS";"USB-C-16P_4LAYER-PADS";"USB Type C 16Pin Connector";"";"";"";"CONN-14122";"";"";"";"";"";
"J6";"Start Base";"CONN_02-JST-2MM-SMT";"JST-2-SMD";"Multi connection point. Often used as Generic Header-pin footprint for 0.1 inch spaced/style header connections";"";"";"";"CONN-11443";"";"";"";"";"";
"J7";"Power Switch";"CONN_02-JST-2MM-SMT";"JST-2-SMD";"Multi connection point. Often used as Generic Header-pin footprint for 0.1 inch spaced/style header connections";"";"";"";"CONN-11443";"";"";"";"";"";
"J8";"";"JST_2MM_MALE";"JST-2-SMD";"JST 2MM MALE RA CONNECTOR";"";"";"";"CONN-11443";"";"PRT-08612";"";"";"";
"J9";"";"CONN_04JST-SMD-LOCKING";"JST-4-SMD-1.25MM-LOCKING";"Multi connection point. Often used as Generic Header-pin footprint for 0.1 inch spaced/style header connections";"";"";"";"CONN-15303";"";"";"";"";"";
"J10";"";"CONN_021X02_NO_SILK";"1X02_NO_SILK";"Multi connection point. Often used as Generic Header-pin footprint for 0.1 inch spaced/style header connections";"";"";"";"";"";"";"";"";"";
"J11";"";"CONN_041X04_NO_SILK_NO_POP";"1X04_NO_SILK";"Multi connection point. Often used as Generic Header-pin footprint for 0.1 inch spaced/style header connections";"";"";"";"";"";"";"";"";"";
"J12";"";"CONN_041X04_NO_SILK_NO_POP";"1X04_NO_SILK";"Multi connection point. Often used as Generic Header-pin footprint for 0.1 inch spaced/style header connections";"";"";"";"";"";"";"";"";"";
"J13";"Internal";"I2C_STANDARDQWIIC";"JST04_1MM_RA";"SparkFun I2C Standard Pinout Header";"";"";"";"CONN-13694";"";"";"";"Qwiic Right Angle";"";
"J14";"";"CONN_021X02_NO_SILK";"1X02_NO_SILK";"Multi connection point. Often used as Generic Header-pin footprint for 0.1 inch spaced/style header connections";"";"";"";"";"";"";"";"";"";
"J15";"";"CONN_021X02_NO_SILK";"1X02_NO_SILK";"Multi connection point. Often used as Generic Header-pin footprint for 0.1 inch spaced/style header connections";"";"";"";"";"";"";"";"";"";
"J16";"microSD";"MICRO-SD-SDIOPUSH-PUSH";"MICRO-SD-SOCKET";"microSD Socket for Transflash";"";"";"";"CONN-07820";"";"";"";"";"";
"J17";"Qwiic Right Angle";"I2C_STANDARD_NO_SILK";"1X04_NO_SILK";"SparkFun I2C Standard Pinout Header";"";"";"";"";"";"";"";"";"";
"J18";"";"CONN_05NO_SILK";"1X05_NO_SILK";"Multi connection point. Often used as Generic Header-pin footprint for 0.1 inch spaced/style header connections";"";"";"";"";"";"";"";"";"";
"JP21";"FIDUCIALUFIDUCIAL";"FIDUCIALUFIDUCIAL";"FIDUCIAL-MICRO";"Fiducial Alignment Points";"";"";"";"";"";"";"";"";"";
"JP61";"FIDUCIALUFIDUCIAL";"FIDUCIALUFIDUCIAL";"FIDUCIAL-MICRO";"Fiducial Alignment Points";"";"";"";"";"";"";"";"";"";
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
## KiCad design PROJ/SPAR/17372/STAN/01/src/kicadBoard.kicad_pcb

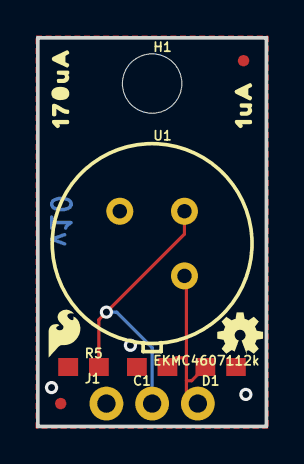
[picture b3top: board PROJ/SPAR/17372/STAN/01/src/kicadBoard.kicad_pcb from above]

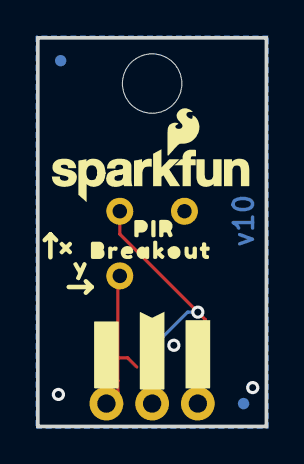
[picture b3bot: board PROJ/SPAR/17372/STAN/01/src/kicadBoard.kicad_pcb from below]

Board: 2 copper layers, 12.7 x 21.6 mm, 23 parts (10 on the bottom side), 3 nets.

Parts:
C1: 0.1uF; 0603
D1: 24V; 0603
FRAME1: FRAME-LETTER; CREATIVE_COMMONS
H1: STAND-OFF
J1: 1X03_NO_SILK
JP2, JP6, JP8, JP9: FIDUCIALUFIDUCIAL; MICRO-FIDUCIAL
LOGO1: OSHW-LOGOMINI; OSHW-LOGO-MINI
LOGO3: SFE_LOGO_NAME_FLAME.1_INCH; SFE_LOGO_NAME_FLAME_.1
LOGO4: SFE_LOGO_FLAME.1_INCH; SFE_LOGO_FLAME_.1
R5: 47k; 0603
U1: EKMC4607112k; TO-3
U$1: #3V3#0
U$2: 170UA0
U$3: #GND#0
U$9: 1UA0
U$11: #OUT#0
U$12: BREAKOUT0
U$13: PIR0
U$14: X0
U$16: Y0

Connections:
3.3V: C1.1, D1.2, J1.3, U1.VDD
GND: C1.2, D1.1, J1.1, R5.1, U1.GND
PIR_OUT: J1.2, R5.2, U1.OUT

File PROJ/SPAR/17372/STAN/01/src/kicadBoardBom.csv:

"Id";"Designator";"Package";"Quantity";"Designation";"Supplier and ref";
1;"FRAME1";"CREATIVE_COMMONS";1;"FRAME-LETTER";;;
2;"R5";"0603";1;"47k";;;
3;"U$2";"170UA0";1;"";;;
4;"U$9";"1UA0";1;"";;;
5;"LOGO1";"OSHW-LOGO-MINI";1;"OSHW-LOGOMINI";;;
6;"U1";"TO-3";1;"EKMC4607112k";;;
7;"H1";"STAND-OFF";1;"STAND-OFF";;;
8;"J1";"1X03_NO_SILK";1;"";;;
9;"D1";"0603";1;"24V";;;
10;"LOGO4";"SFE_LOGO_FLAME_.1";1;"SFE_LOGO_FLAME.1_INCH";;;
11;"JP9,JP8,JP2,JP6";"MICRO-FIDUCIAL";4;"FIDUCIALUFIDUCIAL";;;
12;"C1";"0603";1;"0.1uF";;;
13;"U$11";"#OUT#0";1;"";;;
14;"U$3";"#GND#0";1;"";;;
15;"LOGO3";"SFE_LOGO_NAME_FLAME_.1";1;"SFE_LOGO_NAME_FLAME.1_INCH";;;
16;"U$12";"BREAKOUT0";1;"";;;
17;"U$13";"PIR0";1;"";;;
18;"U$1";"#3V3#0";1;"";;;
19;"U$16";"Y0";1;"";;;
20;"U$14";"X0";1;"";;;

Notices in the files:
parts and their libraries:
RELEASED UNDER THE CREATIVE COMMONS ATTRIBUTION SHARE-ALIKE 4.0 LICENSE
HTTPS://CREATIVECOMMONS.ORG/LICENSES/BY-SA/4.0
